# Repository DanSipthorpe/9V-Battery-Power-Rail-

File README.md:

# 9V-Battery-Power-Rail-
DC/DC switch mode PSU circuit that from a singular 9V battery creates three power rails (+24V, +12V, +5V) for use in battery powered applications 

Please see .docx file for brief overview of project and design process. :)

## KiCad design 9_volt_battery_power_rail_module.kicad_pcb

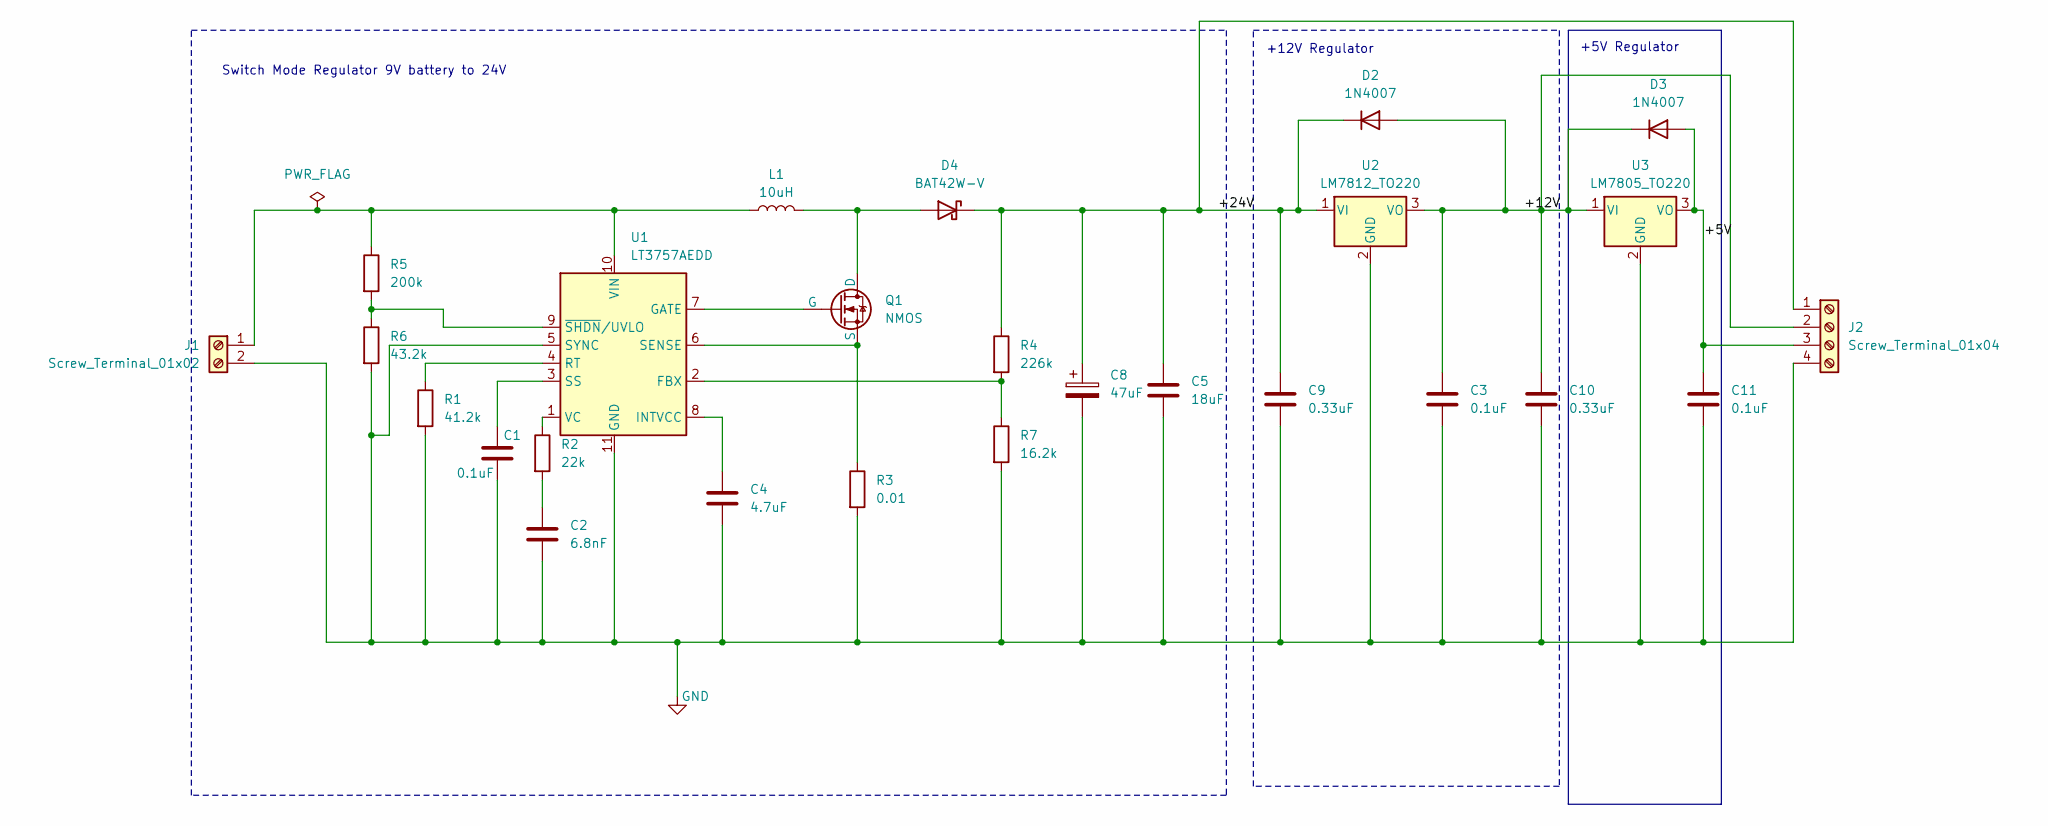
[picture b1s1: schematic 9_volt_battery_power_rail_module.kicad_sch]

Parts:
C1, C3, C11: 0.1uF; C_0805_2012Metric
C2: 6.8nF; C_0805_2012Metric
C4: 4.7uF; C_0805_2012Metric
C5: 18uF; C_0805_2012Metric
C8: 47uF; CP_Radial_D10.0mm_P5.00mm
C9, C10: 0.33uF; C_0805_2012Metric
D2, D3: 1N4007; D_DO-41_SOD81_P10.16mm_Horizontal
D4: BAT42W-V; D_SOD-123
J1: Screw_Terminal_01x02; TerminalBlock_Xinya_XY308-2.54-2P_1x02_P2.54mm_Horizontal
J2: Screw_Terminal_01x04; TerminalBlock_Xinya_XY308-2.54-4P_1x04_P2.54mm_Horizontal
L1: 10uH; L_6.3x6.3_H3
Q1: NMOS; ATPAK-2
R1: 41.2k; R_1206_3216Metric
R2: 22k; R_1206_3216Metric
R3: 0.01; R_1206_3216Metric
R4: 226k; R_1206_3216Metric
R5: 200k; R_1206_3216Metric
R6: 43.2k; R_1206_3216Metric
R7: 16.2k; R_1206_3216Metric
U1: LT3757AEDD; DFN-10-1EP_3x3mm_P0.5mm_EP1.55x2.48mm
U2: LM7812_TO220; TO-220-3_Vertical
U3: LM7805_TO220; TO-220-3_Vertical

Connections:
/+5V: C11.1, D3.2 (A), J2.3, U3.3 (VO)
/+12V: C3.1, C10.1, D2.2 (A), D3.1 (K), J2.2, U2.3 (VO), U3.1 (VI)
/+24V: C5.1, C8.1, C9.1, D2.1 (K), D4.1 (K), J2.1, R4.1, U2.1 (VI)
GND: C1.2, C2.2, C3.2, C4.2, C5.2, C8.2, C9.2, C10.2, C11.2, J1.2, J2.4, R1.2, R3.2, R6.2, R7.2, U1.5 (SYNC), U1.11 (GND), U2.2 (GND), U3.2 (GND)
unnamed: C2.1, R2.2
unnamed: D4.2 (A), L1.2, Q1.1 (D)
unnamed: J1.1, L1.1, R5.1, U1.10 (VIN)
unnamed: Q1.2 (G), U1.7 (GATE)
unnamed: Q1.3 (S), R3.1, U1.6 (SENSE)
unnamed: R4.2, R7.1, U1.2 (FBX)
unnamed: C4.1, U1.8 (INTVCC)
unnamed: R1.1, U1.4 (RT)
unnamed: C1.1, U1.3 (SS)
unnamed: R2.1, U1.1 (VC)
unnamed: R5.2, R6.1, U1.9 (~SHDN/UVLO)

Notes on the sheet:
+5V Regulator
Switch Mode Regulator 9V battery to 24V
+12V Regulator

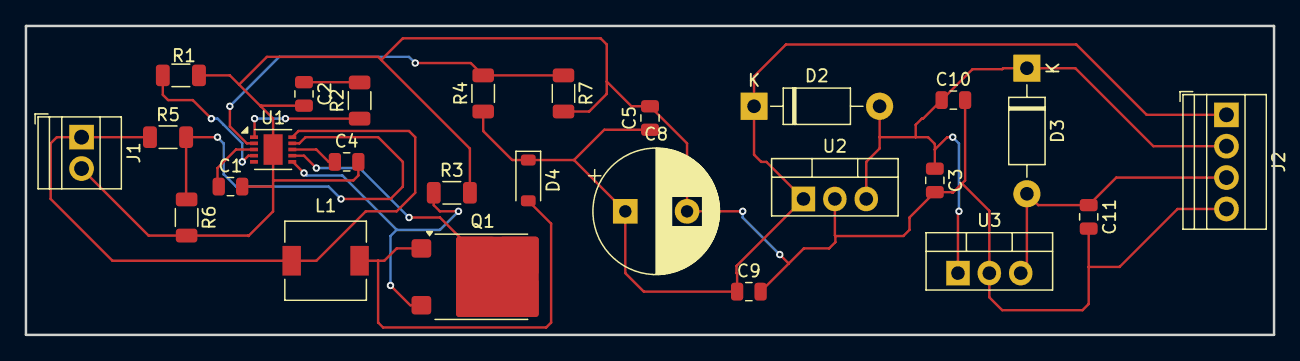
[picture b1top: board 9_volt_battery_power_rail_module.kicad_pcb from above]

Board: 2 copper layers, 101.0 x 25.0 mm, 26 parts (0 on the bottom side), 15 nets.
